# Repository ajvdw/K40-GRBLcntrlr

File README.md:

# K40 GRBL cntrlr
 K40 ESP32 GRBL Controller.
 
This is a replacement for the M2 Nano controller. 
It supports GRBL 1.1 and raster engraving with grayscales.
Since the controller is based on ESP32 it supports Serial, Bluetooth and Wifi communications as well as working offline through the use of an SDCard. 
Designed with DIY in mind, all through-hole components or through-hole modules.

Firmware is forked from https://github.com/bdring/Grbl_Esp32, I only added a machine definition to it. Instructions how to build the software can be found there as well.

K40 GRBLCNTRLR v0.9 in situ.

## B.O.M.

- 1x PCB
- 1x Ttgo Wemos Mini D1 ESP32 Wifi + Bluetooth CP2104 Module
- 2x StepStick DRV8825 or A4988
- 2x resistor 4K7 1/4W
- 1x resistor 100K 1/4W
- 2x elect.cap. 47uF 36V
- 1x MOSFET N-Channel p75nf75 (similar to TO220)
- 1x 1.25Mm Ffc/Fpc Connector 12P
- 2x JST XH2.54 4P 
- 1x JST XH2.54 5P 
- 1x Micro Sd Tf Card Memory Shield Module SPI for Arduino 3.3V
- 1x Term.conn 5.1mm 4P

Total cost should be less than 20$.

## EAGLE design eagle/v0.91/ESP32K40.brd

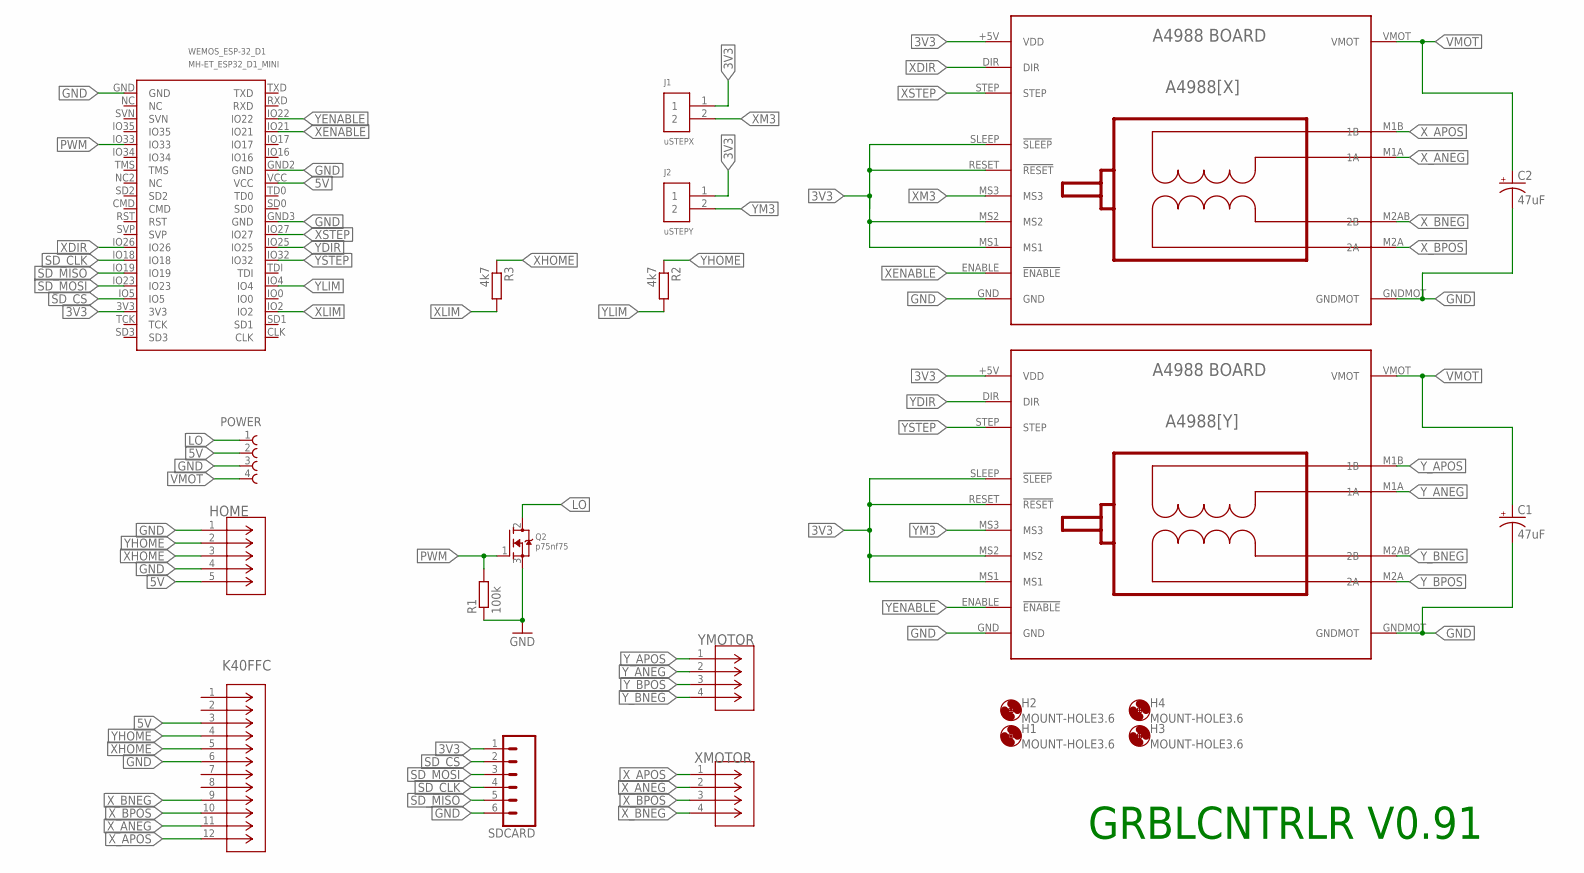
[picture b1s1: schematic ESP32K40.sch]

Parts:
A4988[X]: XMOTOR; BOARD_A4988
A4988[Y]: YMOTOR; BOARD_A4988
C1, C2: 47uF; TAP5-70
H1, H2, H3, H4: MOUNT-HOLE3.6; 3,6
HOME: B5B-XH-A(LF)(SN); CONN_B5B-XH-A(LF)(SN)_JST
J1: uSTEPX; 61300211121
J2: uSTEPY; 61300211121
K40FFC: 1-84534-2; CON12_TH_FCC-FPC2
POWER: 691371700004B
Q2: p75nf75; TO220V
R1: 100k; V234/12
R2, R3: 4k7; V234/12
SDCARD: CONN_06LONGPADS; 1X06_LONGPADS
WEMOS_ESP-32_D1: MH-ET_ESP32_D1_MINI
XMOTOR: B4B-XH-A_(LF)(SN); CONN_B4B-XH-A_(LF)(SN)_JST
YMOTOR: B4B-XH-A_(LF)(SN); CONN_B4B-XH-A_(LF)(SN)_JST

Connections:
3V3: A4988[X].+5V (VDD), A4988[X].MS1, A4988[X].MS2, A4988[X].RESET (!RESET), A4988[X].SLEEP (!SLEEP), A4988[Y].+5V (VDD), A4988[Y].MS1, A4988[Y].MS2, A4988[Y].RESET (!RESET), A4988[Y].SLEEP (!SLEEP), J1.1, J2.1, SDCARD.1, WEMOS_ESP-32_D1.3V3
5V: HOME.5, K40FFC.3, POWER.2, WEMOS_ESP-32_D1.VCC
GND: A4988[X].GND, A4988[X].GNDMOT, A4988[Y].GND, A4988[Y].GNDMOT, C1.-, C2.-, HOME.1, HOME.4, K40FFC.6, POWER.3, Q2.3 (S), R1.1, SDCARD.6, WEMOS_ESP-32_D1.GND, WEMOS_ESP-32_D1.GND2 (GND), WEMOS_ESP-32_D1.GND3 (GND)
LO: POWER.1, Q2.2 (D)
PWM: Q2.1 (G), R1.2, WEMOS_ESP-32_D1.IO33
SD_CLK: SDCARD.4, WEMOS_ESP-32_D1.IO18
SD_CS: SDCARD.2, WEMOS_ESP-32_D1.IO5
SD_MISO: SDCARD.5, WEMOS_ESP-32_D1.IO19
SD_MOSI: SDCARD.3, WEMOS_ESP-32_D1.IO23
VMOT: A4988[X].VMOT, A4988[Y].VMOT, C1.+, C2.+, POWER.4
XDIR: A4988[X].DIR, WEMOS_ESP-32_D1.IO26
XENABLE: A4988[X].ENABLE (!ENABLE), WEMOS_ESP-32_D1.IO21
XHOME: HOME.3, K40FFC.5, R3.1
XLIM: R3.2, WEMOS_ESP-32_D1.IO2
XM3: A4988[X].MS3, J1.2
XSTEP: A4988[X].STEP, WEMOS_ESP-32_D1.IO27
X_ANEG: A4988[X].M1A (1A), K40FFC.11, XMOTOR.2
X_APOS: A4988[X].M1B (1B), K40FFC.12, XMOTOR.1
X_BNEG: A4988[X].M2AB (2B), K40FFC.9, XMOTOR.4
X_BPOS: A4988[X].M2A (2A), K40FFC.10, XMOTOR.3
YDIR: A4988[Y].DIR, WEMOS_ESP-32_D1.IO25
YENABLE: A4988[Y].ENABLE (!ENABLE), WEMOS_ESP-32_D1.IO22
YHOME: HOME.2, K40FFC.4, R2.1
YLIM: R2.2, WEMOS_ESP-32_D1.IO4
YM3: A4988[Y].MS3, J2.2
YSTEP: A4988[Y].STEP, WEMOS_ESP-32_D1.IO32
Y_ANEG: A4988[Y].M1A (1A), YMOTOR.2
Y_APOS: A4988[Y].M1B (1B), YMOTOR.1
Y_BNEG: A4988[Y].M2AB (2B), YMOTOR.4
Y_BPOS: A4988[Y].M2A (2A), YMOTOR.3

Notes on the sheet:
GRBLCNTRLR V0.91

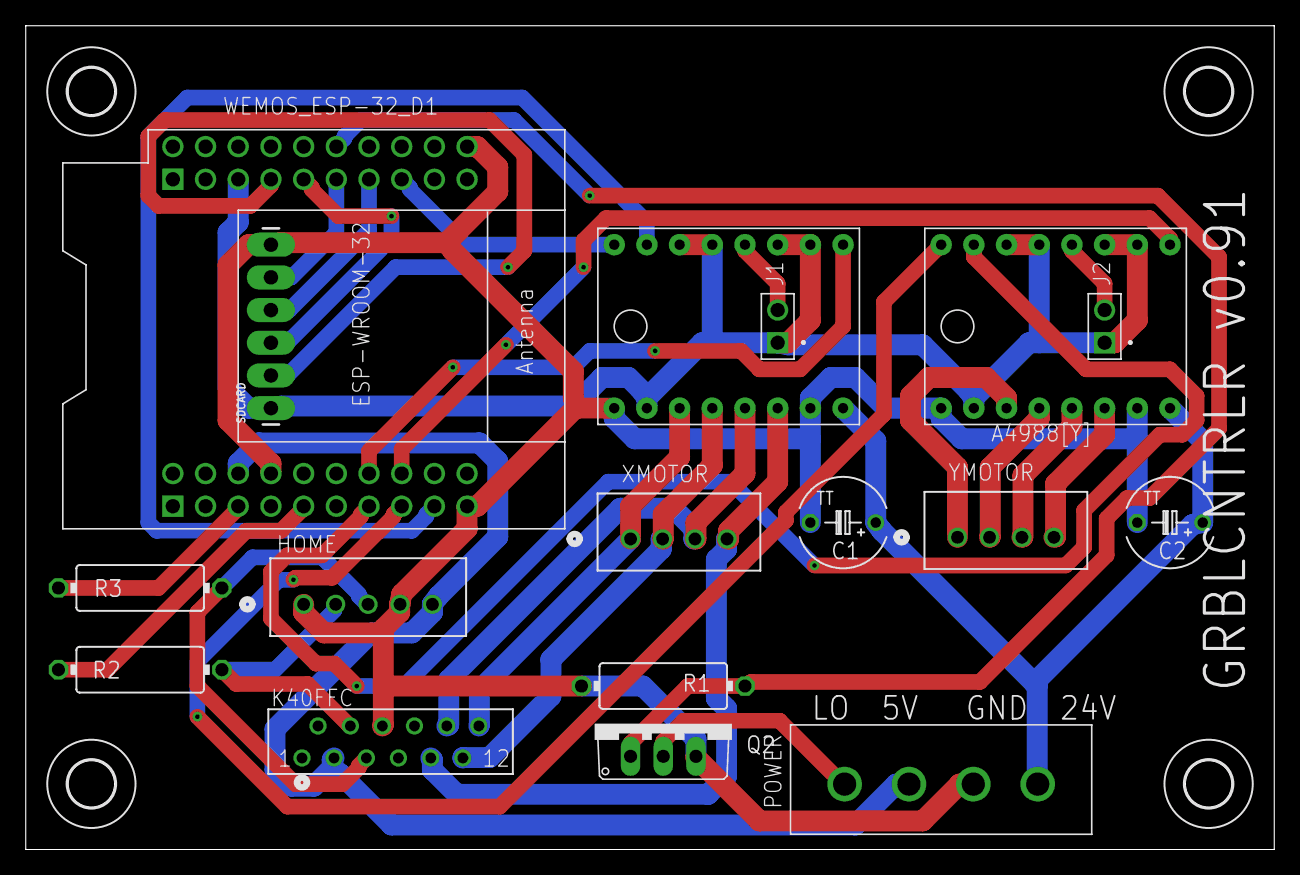
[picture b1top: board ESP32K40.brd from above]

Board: 2 copper layers, 97.0 x 64.0 mm, 21 parts (0 on the bottom side), 30 nets.

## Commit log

2021-07-14 Initial version
2021-07-14 Added photo
2021-07-14 smaller image
2021-07-19 proper mosfet type
2021-07-19 changed mosfet type

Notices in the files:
parts and their libraries:
Wurth_Elektronik_Electromechanic_Termina: Copyright: Würth Elektronik
SparkFun-Connectors: Licensing: Creative Commons ShareAlike 4.0 International - https://creativecommons.org/licenses/by-sa/4.0
COPYRIGHT: Copyright (C) 2018 Accelerated Designs. All rights reserved
